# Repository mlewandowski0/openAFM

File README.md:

# openAFM

for completion also is required : 
- stm32f373 dev board ( I used STM32F373C8T6 board). External DAC for next iterations for better performance is required ( STM32F373 has 16-bit ADC but 12-bit DAC)
- DDS module for preamplifer (I used AD9833 board, also tested AD9850, both works fine). Both are rather expensive IC's but cheap module can be found on aliexpress or equivalent ( they work reasonably well)
- CD4046 board for PLL ( currently on breadboard, design and PCB will be released )

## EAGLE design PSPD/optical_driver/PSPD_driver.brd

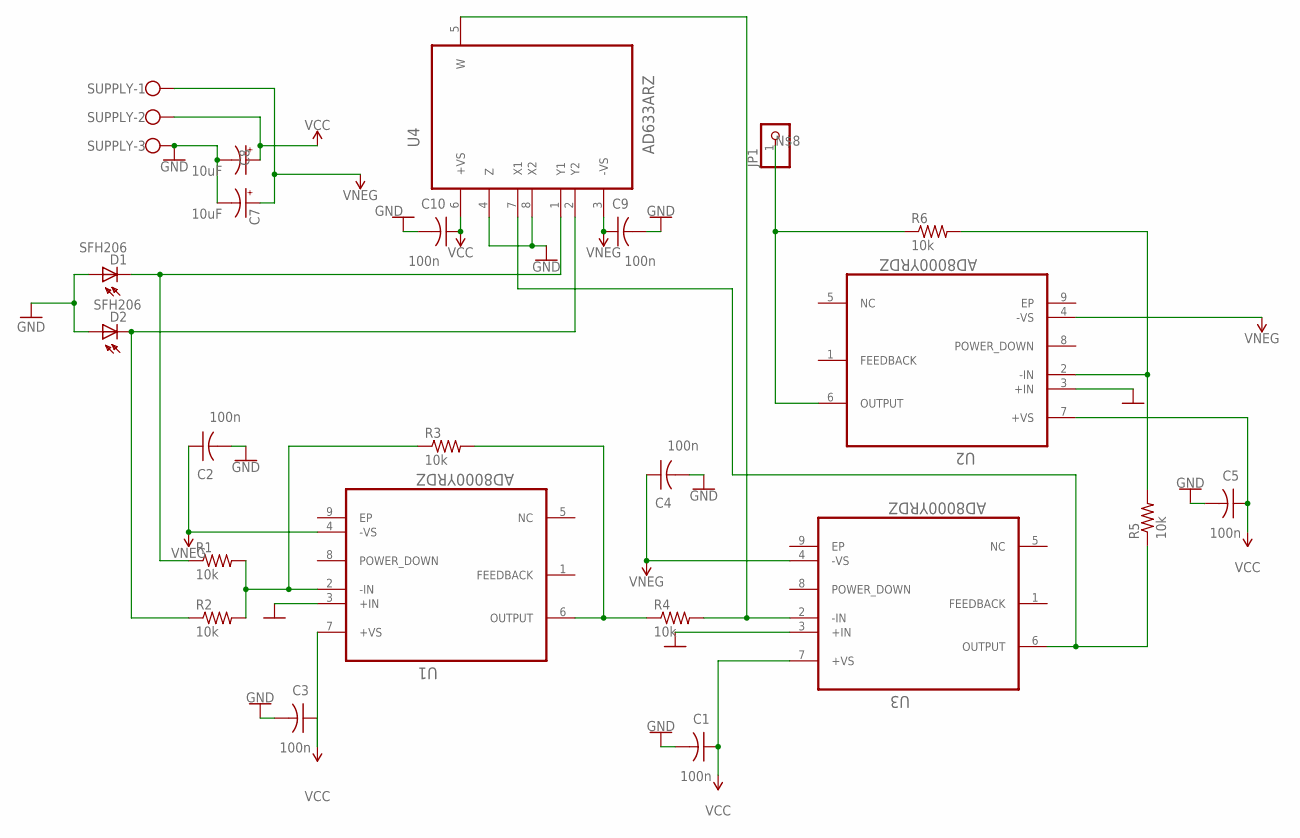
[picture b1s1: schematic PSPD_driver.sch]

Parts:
C1, C2, C3, C4, C5, C9, C10: 100n; C0805K
C7, C8: 10uF; CPOL-RADIAL-2.5MM-5MM
D1, D2: SFH206
JP1: PINHD-1X1; 1X01
R1, R2, R3, R4, R5, R6: 10k; M0805
SUPPLY: W237-103
U1, U2, U3: AD8000YRDZ; SOIC127P600X175-9N
U4: AD633ARZ; SOIC127P600X175-8N

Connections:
GND: C1.2, C2.2, C3.2, C4.2, C5.2, C7.2 (-), C8.2 (-), C9.2, C10.2, D1.A, D2.A, SUPPLY.3, U1.3 (+IN), U2.3 (+IN), U3.3 (+IN), U4.4 (Z), U4.8 (X2)
unnamed: R1.2, R2.2, R3.1, U1.2 (-IN)
unnamed: D1.K (C), R1.1, U4.1 (Y1)
unnamed: D2.K (C), R2.1, U4.2 (Y2)
unnamed: R3.2, R4.1, U1.6 (OUTPUT)
unnamed: R4.2, U3.2 (-IN), U4.5 (W)
unnamed: R5.1, U3.6 (OUTPUT), U4.7 (X1)
unnamed: R5.2, R6.2, U2.2 (-IN)
unnamed: JP1.1, R6.1, U2.6 (OUTPUT)
VCC: C1.1, C3.1, C5.1, C8.1 (+), C10.1, SUPPLY.2, U1.7 (+VS), U2.7 (+VS), U3.7 (+VS), U4.6 (+VS)
VNEG: C2.1, C4.1, C7.1 (+), C9.1, SUPPLY.1, U1.4 (-VS), U2.4 (-VS), U3.4 (-VS), U4.3 (-VS)

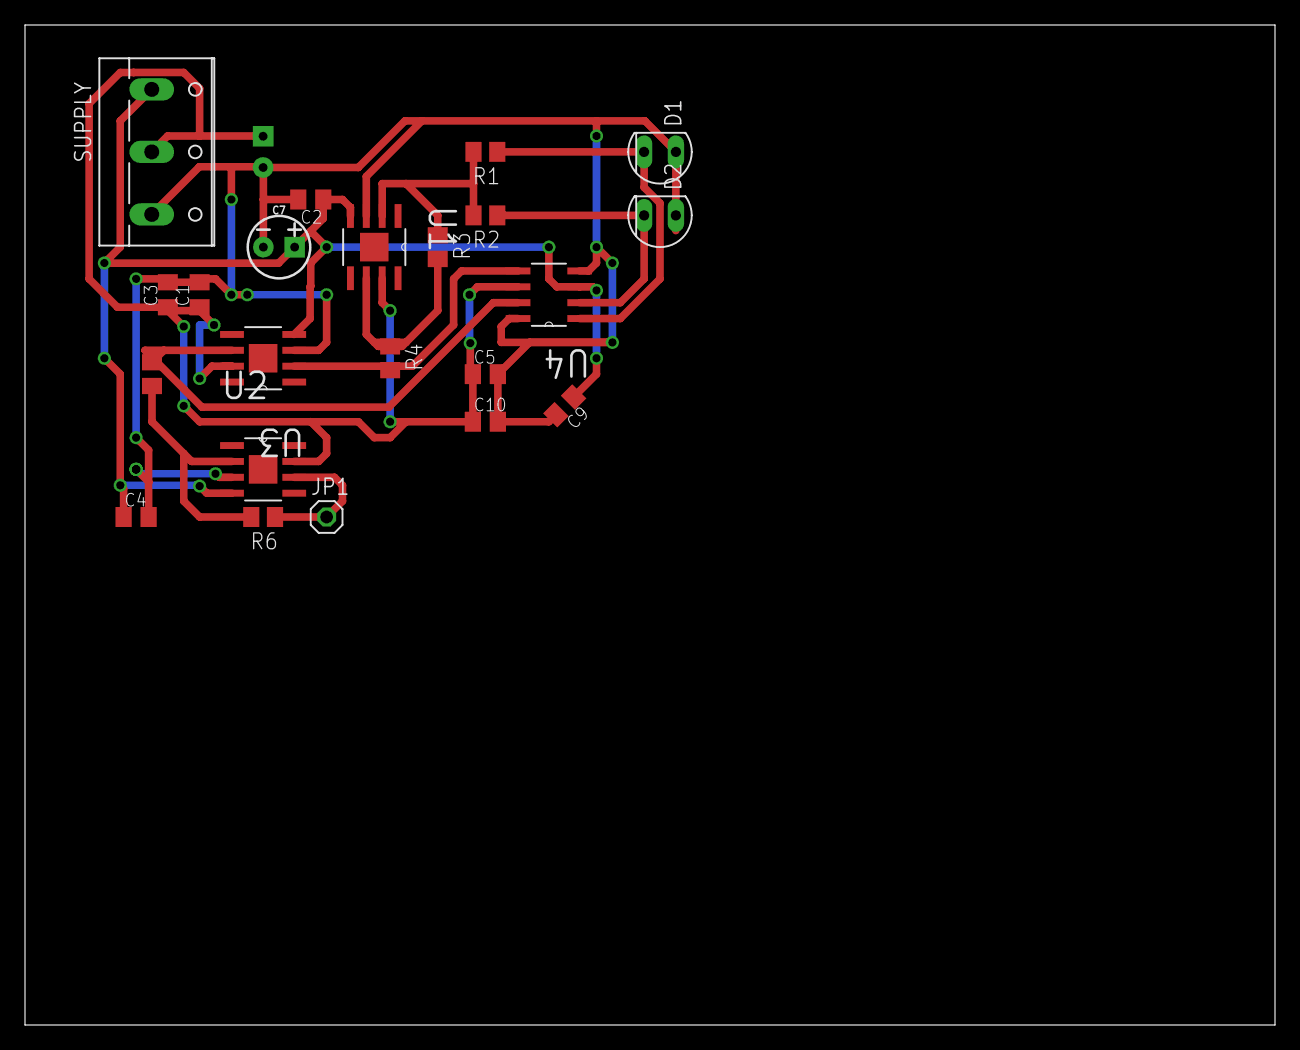
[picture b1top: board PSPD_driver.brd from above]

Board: 2 copper layers, 100.0 x 80.0 mm, 23 parts (1 on the bottom side), 11 nets.

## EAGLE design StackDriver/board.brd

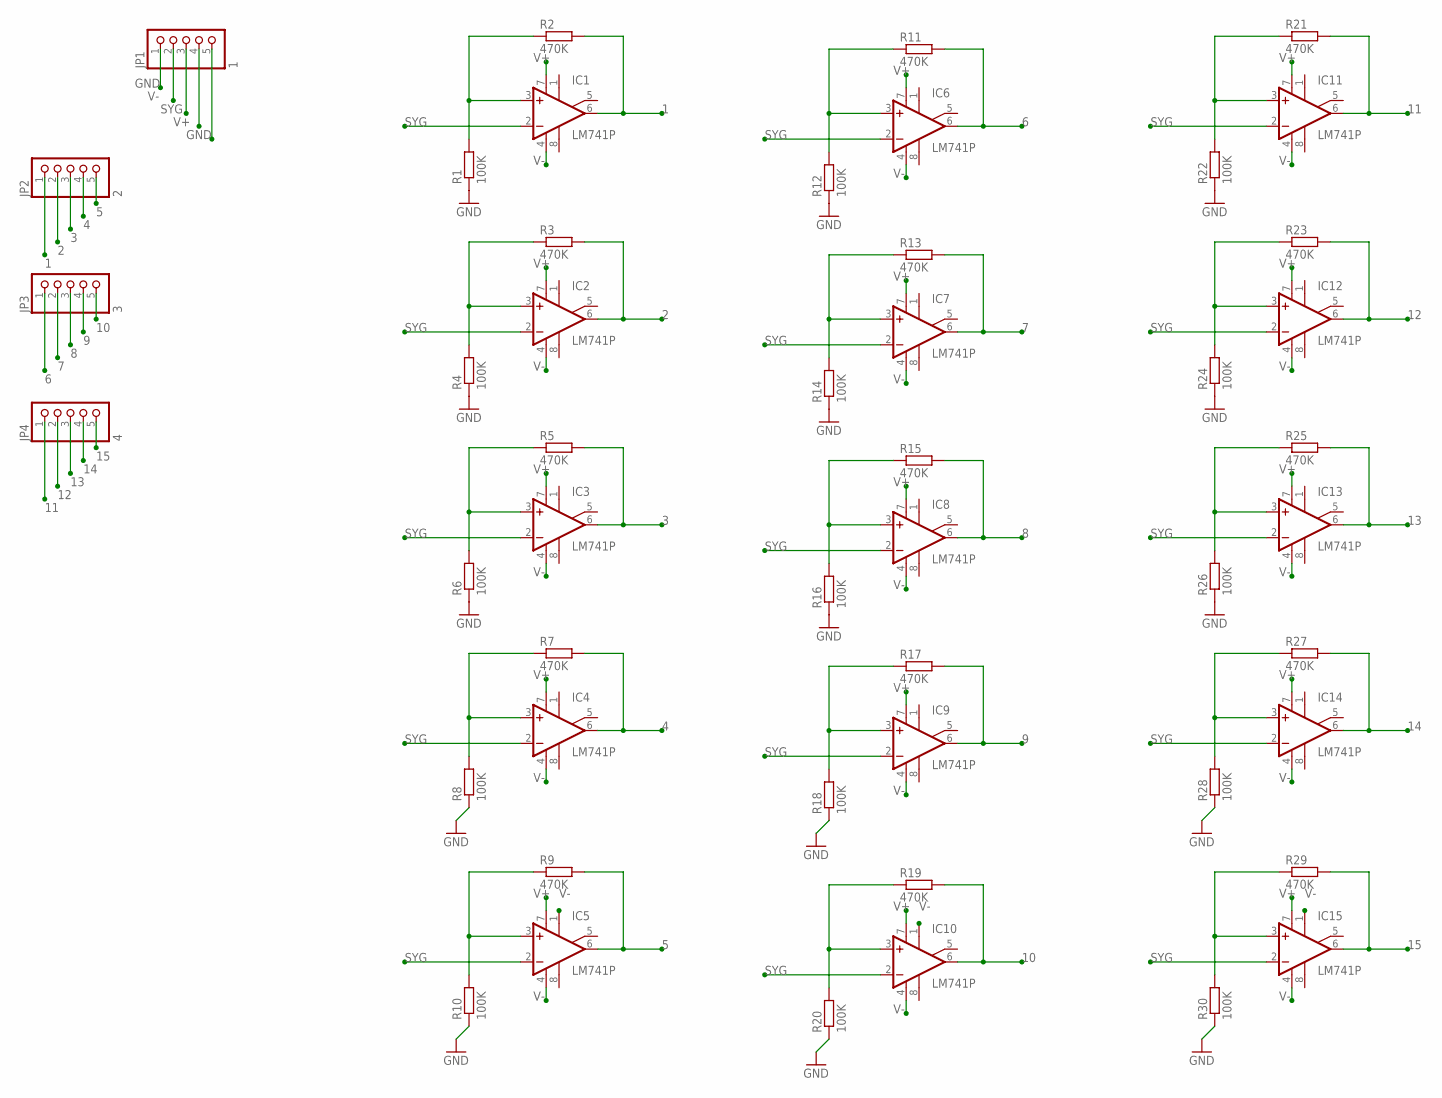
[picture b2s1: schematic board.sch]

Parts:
IC1, IC2, IC3, IC4, IC5, IC6, IC7, IC8, IC9, IC10, IC11, IC12, IC13, IC14, IC15: LM741P; DIL08
JP1: 1; 1X05
JP2: 2; 1X05
JP3: 3; 1X05
JP4: 4; 1X05
R1, R4, R6, R8, R10, R12, R14, R16, R18, R20, R22, R24, R26, R28, R30: 100K; 0204/7
R2, R3, R5, R7, R9, R11, R13, R15, R17, R19, R21, R23, R25, R27, R29: 470K; 0204/7

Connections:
1: IC1.6 (OUT), JP2.1, R2.2
2: IC2.6 (OUT), JP2.2, R3.2
3: IC3.6 (OUT), JP2.3, R5.2
4: IC4.6 (OUT), JP2.4, R7.2
5: IC5.6 (OUT), JP2.5, R9.2
6: IC6.6 (OUT), JP3.1, R11.2
7: IC7.6 (OUT), JP3.2, R13.2
8: IC8.6 (OUT), JP3.3, R15.2
9: IC9.6 (OUT), JP3.4, R17.2
10: IC10.6 (OUT), JP3.5, R19.2
11: IC11.6 (OUT), JP4.1, R21.2
12: IC12.6 (OUT), JP4.2, R23.2
13: IC13.6 (OUT), JP4.3, R25.2
14: IC14.6 (OUT), JP4.4, R27.2
15: IC15.6 (OUT), JP4.5, R29.2
GND: JP1.1, JP1.5, R1.1, R4.1, R6.1, R8.1, R10.1, R12.1, R14.1, R16.1, R18.1, R20.1, R22.1, R24.1, R26.1, R28.1, R30.1
unnamed: IC2.3 (+IN), R3.1, R4.2
unnamed: IC1.3 (+IN), R1.2, R2.1
unnamed: IC3.3 (+IN), R5.1, R6.2
unnamed: IC4.3 (+IN), R7.1, R8.2
unnamed: IC5.3 (+IN), R9.1, R10.2
unnamed: IC6.3 (+IN), R11.1, R12.2
unnamed: IC7.3 (+IN), R13.1, R14.2
unnamed: IC8.3 (+IN), R15.1, R16.2
unnamed: IC9.3 (+IN), R17.1, R18.2
unnamed: IC10.3 (+IN), R19.1, R20.2
unnamed: IC11.3 (+IN), R21.1, R22.2
unnamed: IC12.3 (+IN), R23.1, R24.2
unnamed: IC13.3 (+IN), R25.1, R26.2
unnamed: IC14.3 (+IN), R27.1, R28.2
unnamed: IC15.3 (+IN), R29.1, R30.2
SYG: IC1.2 (-IN), IC2.2 (-IN), IC3.2 (-IN), IC4.2 (-IN), IC5.2 (-IN), IC6.2 (-IN), IC7.2 (-IN), IC8.2 (-IN), IC9.2 (-IN), IC10.2 (-IN), IC11.2 (-IN), IC12.2 (-IN), IC13.2 (-IN), IC14.2 (-IN), IC15.2 (-IN), JP1.3
V+: IC1.7 (V+), IC2.7 (V+), IC3.7 (V+), IC4.7 (V+), IC5.7 (V+), IC6.7 (V+), IC7.7 (V+), IC8.7 (V+), IC9.7 (V+), IC10.7 (V+), IC11.7 (V+), IC12.7 (V+), IC13.7 (V+), IC14.7 (V+), IC15.7 (V+), JP1.4
V-: IC1.4 (V-), IC2.4 (V-), IC3.4 (V-), IC4.4 (V-), IC5.1 (ON1), IC5.4 (V-), IC6.4 (V-), IC7.4 (V-), IC8.4 (V-), IC9.4 (V-), IC10.1 (ON1), IC10.4 (V-), IC11.4 (V-), IC12.4 (V-), IC13.4 (V-), IC14.4 (V-), IC15.1 (ON1), IC15.4 (V-), JP1.2

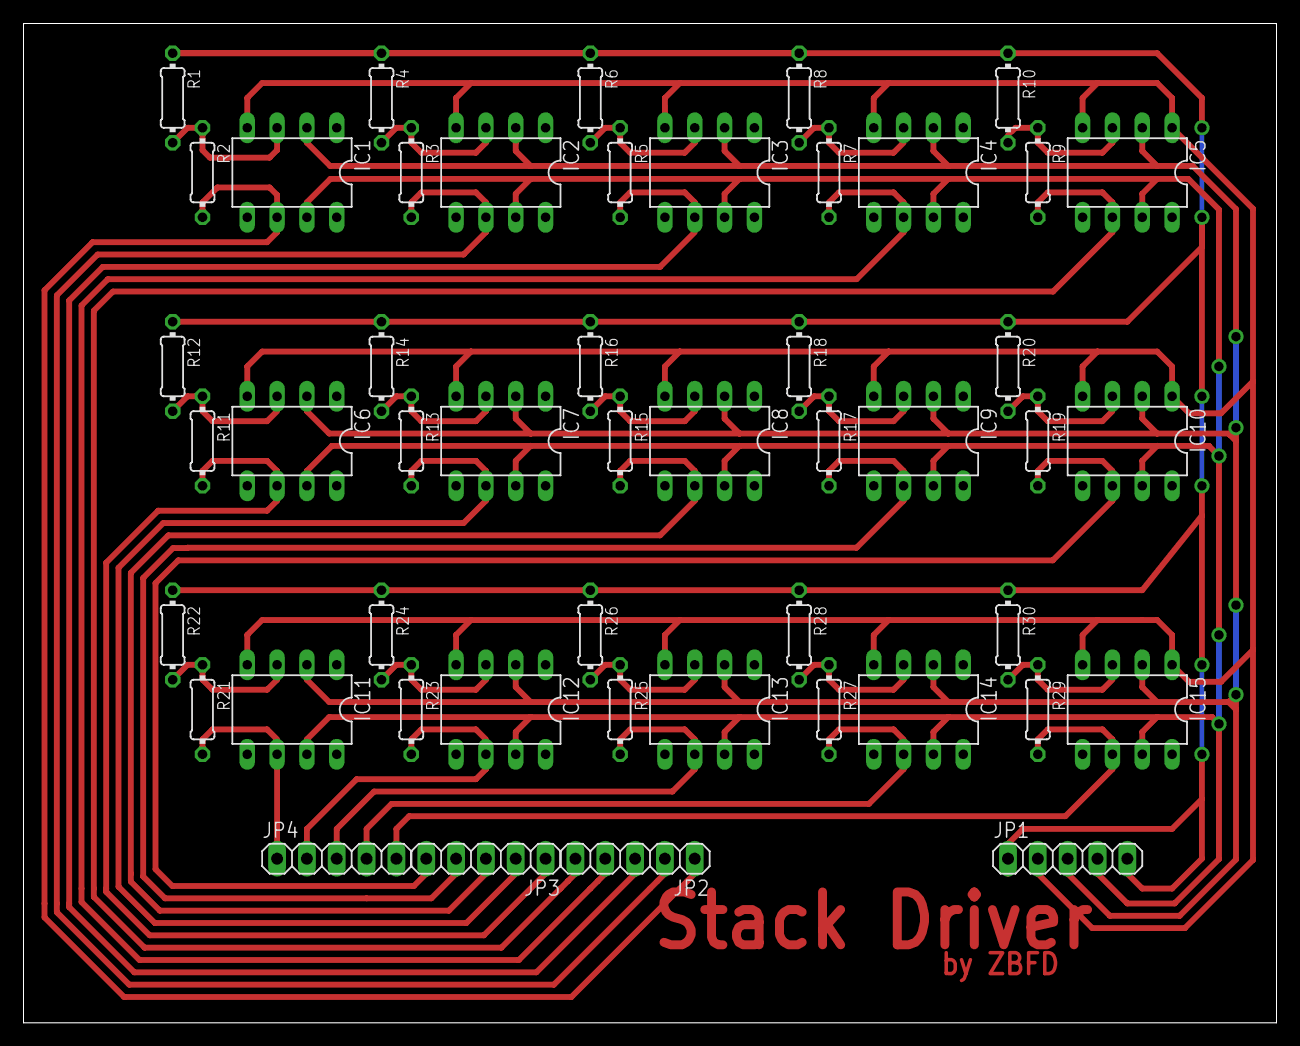
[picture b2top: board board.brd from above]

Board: 2 copper layers, 106.7 x 85.1 mm, 49 parts (0 on the bottom side), 34 nets.

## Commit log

2018-10-09 Add files via upload
    drivers schematics and photodiode schematics
2018-10-14 Schemat i pcb wzmacniacza do piezoelektryka. Niedokończony. Pogrubiam ścieżki
2018-10-14 Zmiana nazwy folderu z Wzmocnienie Piezzo/ na StackDriver. Pogrubione ścieżki 0.5mm i oddzielone 0.55. Schemat skończony
2018-10-14 Brzydko wyglądająca ścieżka przy wejściach: POPRAWIONA
2018-10-15 debug
2018-10-15 add pdf
2018-10-15 good pdf
2018-12-10 PSPD
2020-08-09 OPU, preamplifier for tuning fork, 3d designs, more will follow

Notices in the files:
parts and their libraries:
SparkFun-Capacitors: Licensing: Creative Commons ShareAlike 4.0 International - https://creativecommons.org/licenses/by-sa/4.0
